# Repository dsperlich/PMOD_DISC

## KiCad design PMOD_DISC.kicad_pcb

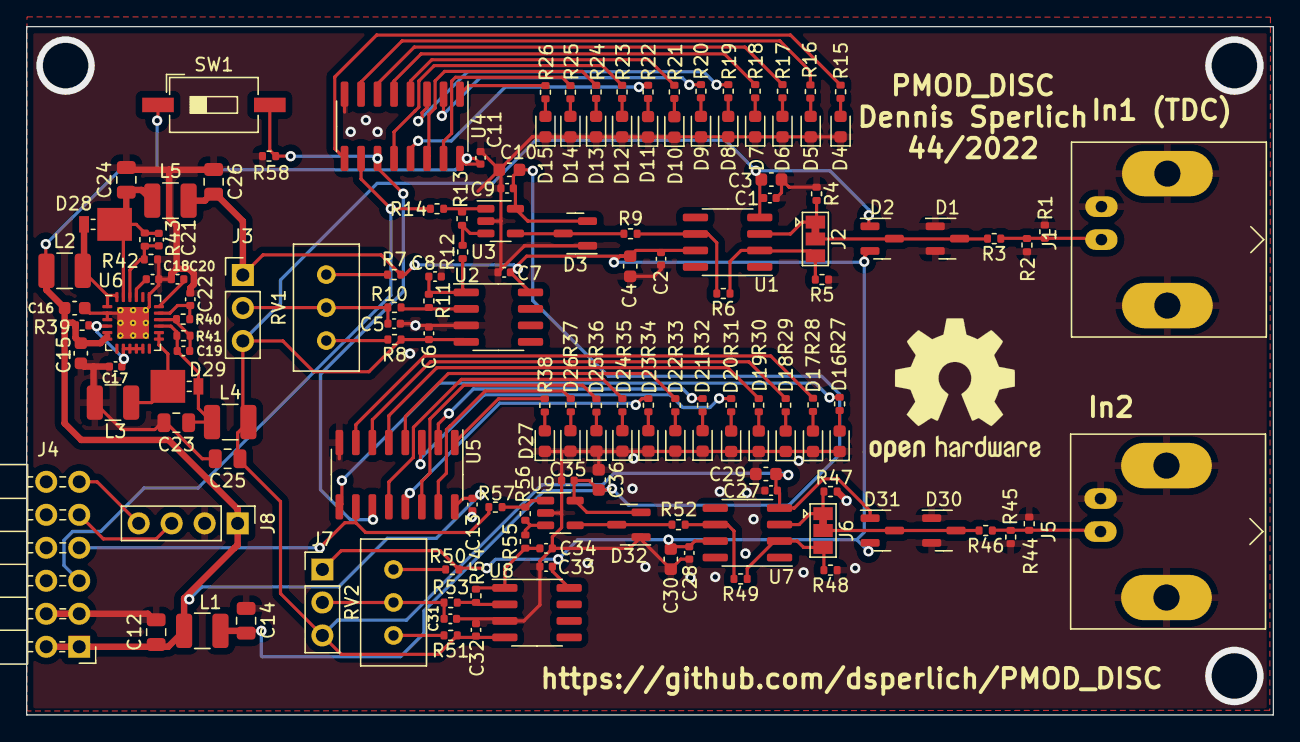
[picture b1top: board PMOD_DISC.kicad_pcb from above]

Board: 2 copper layers, 96.0 x 53.0 mm, 151 parts (0 on the bottom side), 94 nets.

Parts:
C1, C2, C18, C27, C28: 10n; C_0402_1005Metric
C3, C4, C10, C29, C30, C36: 2u2; C_0603_1608Metric
C5, C6, C7, C8, C9, C11, C13, C17, C31, C32, C33, C34, C35: 100n; C_0402_1005Metric
C12, C14, C23, C24, C25, C26: 22u; C_0805_2012Metric
C15, C16: 4u7; C_0603_1608Metric
C19: 7p5; C_0402_1005Metric
C20: 4n7; C_0402_1005Metric
C21: 6p8; C_0402_1005Metric
C22: 220n; C_0402_1005Metric
D1, D2, D3, D30, D31, D32: BAS40-04; SOT-23
D4, D5, D6, D7, D8, D9, D10, D11, D12, D13, D14, D15, D16, D17, D18, D19, D20, D21, D22, D23, D24, D25, D26, D27: LED; LED_0603_1608Metric
D28, D29: MBRM120LT1G; D_Powermite_AK
J1, J5: Conn_Coaxial; BNC_Amphenol_B6252HB-NPP3G-50_Horizontal
J2, J6: Conn_01x03_Male; SolderJumper-3_P1.3mm_Bridged12_Pad1.0x1.5mm
J3, J7: Conn_01x03_Male; PinHeader_1x03_P2.54mm_Vertical
J4: Conn_02x06_Odd_Even; PinHeader_2x06_P2.54mm_Horizontal
J8: Conn_01x04_Male; PinHeader_1x04_P2.54mm_Vertical
L1, L4, L5: 220n; L_1210_3225Metric
L2, L3: 4u7; L_1210_3225Metric
R1, R2, R11, R12, R14, R39, R44, R45, R54, R55, R57: 100R; R_0402_1005Metric
R3, R5, R9, R46, R48, R52: 22R; R_0402_1005Metric
R4, R47: 0R; R_0402_1005Metric
R6, R49: 200R; R_0402_1005Metric
R7, R8, R10, R50, R51, R53: 10k; R_0402_1005Metric
R13, R56: 200k; R_0402_1005Metric
R15, R16, R17, R18, R19, R20, R21, R22, R23, R24, R25, R26, R27, R28, R29, R30, R31, R32, R33, R34, R35, R36, R37, R38, R58: 1k; R_0402_1005Metric
R40: 104k8; R_0402_1005Metric
R41: 1M3; R_0402_1005Metric
R42: 85k8; R_0402_1005Metric
R43: 975k; R_0402_1005Metric
RV1, RV2: 10k; Potentiometer_Bourns_3296W_Vertical
SW1: SW_Push_Dual; SW_DIP_SPSTx01_Slide_6.7x4.1mm_W8.61mm_P2.54mm_LowProfile
U1, U7: LM7171xIM; SOIC-8_3.9x4.9mm_P1.27mm
U2, U8: LM358; SOIC-8_3.9x4.9mm_P1.27mm
U3, U9: MAX999; SOT-23-5
U4, U5: 4040; SOIC-16_3.9x9.9mm_P1.27mm
U6: TPS65130RGE; VQFN-24-1EP_4x4mm_P0.5mm_EP2.45x2.45mm_ThermalVias

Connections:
+3.3V: C11.2, C12.1, C13.2, C15.1, C16.1, J4.1, J4.2, J8.1, L1.1, L2.1, R39.1, SW1.1, U4.16 (VDD), U5.16 (VDD), U6.5 (INN), U6.6 (INN)
+3.3VA: C9.1, C10.1, C14.1, C35.1, C36.1, D3.2, D32.2, L1.2, U3.5 (VCC), U9.5 (VCC)
+15V: C2.1, C4.1, C7.1, C26.1, C28.1, C30.1, C33.1, D2.2, D31.2, J3.1, J7.1, L5.2, R7.2, R50.2, U1.7 (V+), U2.8 (V+), U7.7 (V+), U8.8 (V+)
-15V: C1.1, C3.1, C6.1, C25.1, C27.1, C29.1, C32.1, D2.1, D31.1, J3.3, J7.3, L4.2, R8.1, R51.1, U1.4 (V-), U2.4 (V-), U7.4 (V-), U8.4 (V-)
/ConPower/OUT1: J4.5, R14.2, U4.10 (CLK)
/ConPower/OUT2: J4.7, R57.2, U5.10 (CLK)
/ConPower/SCL: J4.9, J8.3
/ConPower/SDA: J4.11, J8.4
GND: C1.2, C2.2, C3.2, C4.2, C5.2, C6.2, C7.2, C8.2, C9.2, C10.2, C11.1, C12.2, C13.1, C14.2, C15.2, C16.2, C17.2, C18.1, C20.1, C22.1, C23.2, C24.2, C25.2, C26.2, C27.2, C28.2, C29.2, C30.2, C31.2, C32.2, C33.2, C34.2, C35.2, C36.2, D1.1, D1.2, D3.1, D4.1 (K), D5.1 (K), D6.1 (K), D7.1 (K), D8.1 (K), D9.1 (K), D10.1 (K), D11.1 (K), D12.1 (K), D13.1 (K), D14.1 (K), D15.1 (K), D16.1 (K), D17.1 (K), D18.1 (K), D19.1 (K), D20.1 (K), D21.1 (K), D22.1 (K), D23.1 (K), D24.1 (K), D25.1 (K), D26.1 (K), D27.1 (K), D30.1, D30.2, D32.1, J1.2 (Ext), J4.3, J4.4, J5.2 (Ext), J8.2, L3.1, R1.2, R2.2, R4.1, R5.1, R42.2, R44.2, R45.2, R47.1, R48.1, R58.1, U2.3 (+), U3.2 (GND), U4.8 (VSS), U5.8 (VSS), U6.2 (PGND), U6.3 (PGND), U6.19 (AGND), U6.25 (EP), U8.3 (+), U9.2 (GND)
unnamed: C5.1, J3.2, R10.1, RV1.2
unnamed: C8.1, R11.2, R12.1, U2.1
unnamed: C17.1, R39.2, U6.4 (VIN), U6.8 (ENP), U6.9 (PSP), U6.10 (ENN), U6.11 (PSN)
unnamed: C18.2, U6.21 (CP)
unnamed: C19.1, C23.1, D29.2 (A), L4.1, R41.2, U6.15 (VNEG)
unnamed: C19.2, R40.2, R41.1, U6.16 (FBN)
unnamed: C20.2, U6.18 (CN)
unnamed: C21.1, R42.1, R43.1, U6.22 (FBP)
unnamed: C21.2, C24.1, D28.1 (K), L5.1, R43.2, U6.23 (VPOS)
unnamed: C22.2, R40.1, U6.17 (VREF)
unnamed: C31.1, J7.2, R53.1, RV2.2
unnamed: C34.1, R54.2, R55.1, U8.1
unnamed: D1.3, D2.3, J2.2, R3.2
unnamed: D3.3, R9.1, U3.4 (IN-)
unnamed: D4.2 (A), R15.2
unnamed: D5.2 (A), R16.2
unnamed: D6.2 (A), R17.2
unnamed: D7.2 (A), R18.2
unnamed: D8.2 (A), R19.2
unnamed: D9.2 (A), R20.2
unnamed: D10.2 (A), R21.2
unnamed: D11.2 (A), R22.2
unnamed: D12.2 (A), R23.2
unnamed: D13.2 (A), R24.2
unnamed: D14.2 (A), R25.2
unnamed: D15.2 (A), R26.2
unnamed: D16.2 (A), R27.2
unnamed: D17.2 (A), R28.2
unnamed: D18.2 (A), R29.2
unnamed: D19.2 (A), R30.2
unnamed: D20.2 (A), R31.2
unnamed: D21.2 (A), R32.2
unnamed: D22.2 (A), R33.2
unnamed: D23.2 (A), R34.2
unnamed: D24.2 (A), R35.2
unnamed: D25.2 (A), R36.2
unnamed: D26.2 (A), R37.2
unnamed: D27.2 (A), R38.2
unnamed: D28.2 (A), L2.2, U6.1 (INP), U6.24 (INP)
unnamed: D29.1 (K), L3.2, U6.13 (OUTN), U6.14 (OUTN)
unnamed: D30.3, D31.3, J6.2, R46.2
unnamed: D32.3, R52.1, U9.4 (IN-)
unnamed: J1.1 (In), R1.1, R2.1, R3.1
unnamed: J2.1, R4.2, U1.3 (+)
unnamed: J2.3, R5.2, R6.1, U1.2 (-)
unnamed: J5.1 (In), R44.1, R45.1, R46.1
unnamed: J6.1, R47.2, U7.3 (+)
unnamed: J6.3, R48.2, R49.1, U7.2 (-)
unnamed: R6.2, R9.2, U1.6
unnamed: R7.1, RV1.1
unnamed: R8.2, RV1.3
unnamed: R10.2, R11.1, U2.2 (-)
unnamed: R12.2, R13.1, U3.3 (IN+)
unnamed: R13.2, R14.1, U3.1 (Q)
unnamed: R15.1, U4.9 (Q0)
unnamed: R16.1, U4.7 (Q1)
unnamed: R17.1, U4.6 (Q2)
unnamed: R18.1, U4.5 (Q3)
unnamed: R19.1, U4.3 (Q4)
unnamed: R20.1, U4.2 (Q5)
unnamed: R21.1, U4.4 (Q6)
unnamed: R22.1, U4.13 (Q7)
unnamed: R23.1, U4.12 (Q8)
unnamed: R24.1, U4.14 (Q9)
unnamed: R25.1, U4.15 (Q10)
unnamed: R26.1, U4.1 (Q11)
unnamed: R27.1, U5.9 (Q0)
unnamed: R28.1, U5.7 (Q1)
unnamed: R29.1, U5.6 (Q2)
unnamed: R30.1, U5.5 (Q3)
unnamed: R31.1, U5.3 (Q4)
unnamed: R32.1, U5.2 (Q5)
unnamed: R33.1, U5.4 (Q6)
unnamed: R34.1, U5.13 (Q7)
unnamed: R35.1, U5.12 (Q8)
unnamed: R36.1, U5.14 (Q9)
unnamed: R37.1, U5.15 (Q10)
unnamed: R38.1, U5.1 (Q11)
unnamed: R49.2, R52.2, U7.6
unnamed: R50.1, RV2.1
unnamed: R51.2, RV2.3
unnamed: R53.2, R54.1, U8.2 (-)
unnamed: R55.2, R56.1, U9.3 (IN+)
unnamed: R56.2, R57.1, U9.1 (Q)
unnamed: R58.2, SW1.2, U4.11 (Reset), U5.11 (Reset)

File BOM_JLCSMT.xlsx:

Comment | Designator | Footprint | JLCPCB Part #（optional）
Conn_01x04_Male | J8 | PinHeader_1x04_P2.54mm_Vertical | C2905435
SN74HC4040DR | U4,U5 | SOIC-16_3.9x9.9mm_P1.27mm | C6848
100n | C17,C35,C33,C32,C31,C13,C11,C9,C7,C6,C5,C34,C8 | C_0402_1005Metric | C307331
4u7 | C16,C15 | C_0603_1608Metric | C19666
MAX999 | U9,U3 | SOT-23-5 | C124667
LM358 | U8,U2 | SOIC-8_3.9x4.9mm_P1.27mm | C7950
LM7171xIM | U7,U1 | SOIC-8_3.9x4.9mm_P1.27mm | C111821
10k | RV2,RV1 | Potentiometer_Bourns_3296W_Vertical | C118954
100R | R57,R55,R54,R45,R44,R39,R14,R12,R11,R2,R1 | R_0402_1005Metric | C25076
200k | R56,R13 | R_0402_1005Metric | C25764
10k | R53,R51,R50,R10,R8,R7 | R_0402_1005Metric | C25744
22R | R52,R48,R46,R9,R5,R3 | R_0402_1005Metric | C25092
200R | R49,R6 | R_0402_1005Metric | C25087
0R | R47,R4 | R_0402_1005Metric
Conn_01x03_Male | J7,J3 | PinHeader_1x03_P2.54mm_Vertical | C49257
Conn_01x03_Male | J6,J2 | SolderJumper-3_P1.3mm_Bridged12_Pad1.0x1.5mm
Conn_Coaxial | J5,J1 | BNC_Amphenol_B6252HB-NPP3G-50_Horizontal | C521205
BAS40-04 | D32,D31,D30,D3,D2,D1 | SOT-23 | C25087
2u2 | C36,C30,C29,C10,C4,C3 | C_0603_1608Metric | C99228
10n | C28,C27,C18,C2,C1 | C_0402_1005Metric | C15195
220n | L5,L4,L1 | L_1210_3225Metric | C295225
4u7 | L3,L2 | L_1210_3225Metric | C295225
MBRM120LT1G | D29,D28 | D_Powermite_AK | C32150
LED | D27,D26,D25,D24,D23,D22,D21,D20,D19,D18,D17,D16,D15,D14,D13,D12,D11,D10,D9,D8,D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 | LED_0603_1608Metric | C2286
Conn_02x06_Odd_Even | J4 | PinHeader_2x06_P2.54mm_Horizontal | C239337
975k | R43 | R_0402_1005Metric | C25802
85k8 | R42 | R_0402_1005Metric | C19709
1M3 | R41 | R_0402_1005Metric | C247060
104k8 | R40 | R_0402_1005Metric | C25742
1k | R58,R38,R37,R36,R35,R34,R33,R32,R31,R30,R29,R28,R27,R26,R25,R24,R23,R22,R21,R20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 | R_0402_1005Metric | C11702
22u | C26,C25,C24,C23,C14,C12 | C_0805_2012Metric | C129303
220n | C22 | C_0402_1005Metric | C16772
6p8 | C21 | C_0402_1005Metric | C1576
4n7 | C20 | C_0402_1005Metric | C1569
7p5 | C19 | C_0402_1005Metric | C388119
TPS65130RGE | U6 | VQFN-24-1EP_4x4mm_P0.5mm_EP2.45x2.45mm_ThermalVias | C87663
SW_DIP_SPSTx01_Slide_6.7x4.1mm_W8.61mm_P2.54mm_LowProfile | SW1 | SW_Push_Dual | C118141

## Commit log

2022-10-30 add counter reset button + cleanup
